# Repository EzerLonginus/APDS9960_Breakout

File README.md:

# APDS9960_Breakout
Breakout for APD29960 Gesture/Prox/Light Sensor.

## Purpose
I had a bunch of these little sensors from an earlier client project.  The project ended up not needed these, and I became the proud owner of a bunch of loose components.  I finally got around to making a simple breakout board for them (It assumes a 3V power source and has no voltage protection of any sort).  
The I2C layout is identical to the OLED boards that I also have a bunch of (and being utilized in the ATTiny412 Metronome project).  The idea being that I could repurpose a metronome board and just plug this in to quickly play with. 

## Scematic

## Layout

## TO DO:
* Populate & test board when it arrives
* Push some test code with the ATTiny412
* Post pictures of finished board

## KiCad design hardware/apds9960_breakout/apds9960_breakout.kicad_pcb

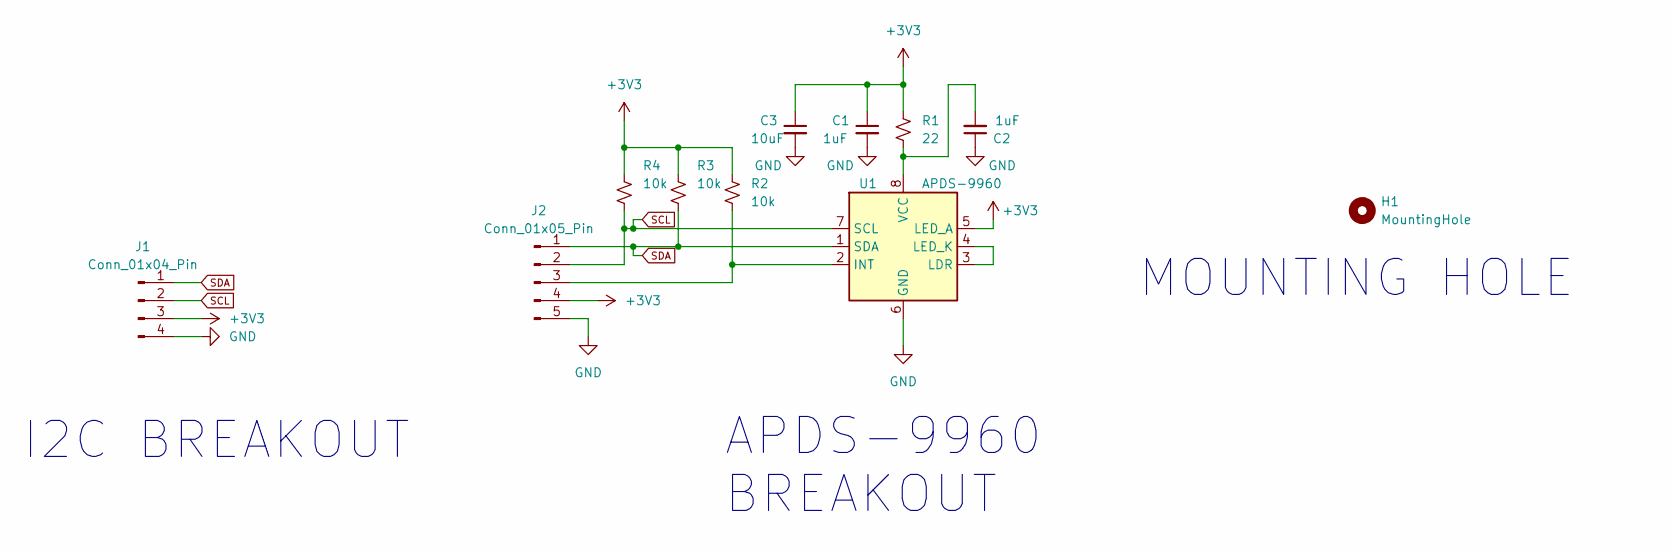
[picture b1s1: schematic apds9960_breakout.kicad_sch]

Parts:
C1, C2: 1uF; C_0603_1608Metric
C3: 10uF; C_0805_2012Metric
H1: MountingHole; MountingHole_3.2mm_M3
J1: Conn_01x04_Pin; PinHeader_1x04_P2.54mm_Vertical
J2: Conn_01x05_Pin; PinHeader_1x05_P2.54mm_Vertical
R1: 22; R_0603_1608Metric
R2, R3, R4: 10k; R_0603_1608Metric
U1: APDS-9960; Avago_APDS-9960

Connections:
+3V3: C1.1, C3.1, J1.3, J2.4, R1.1, R2.1, R3.1, R4.1, U1.5 (LED_A)
GND: C1.2, C2.1, C3.2, J1.4, J2.5, U1.6 (GND)
unnamed: J2.3, R2.2, U1.2 (INT)
unnamed: U1.3 (LDR), U1.4 (LED_K)
unnamed: C2.2, R1.2, U1.8 (VCC)
SCL: J1.2, J2.2, R4.2, U1.7 (SCL)
SDA: J1.1, J2.1, R3.2, U1.1 (SDA)

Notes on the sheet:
I2C BREAKOUT
MOUNTING HOLE
APDS-9960 BREAKOUT

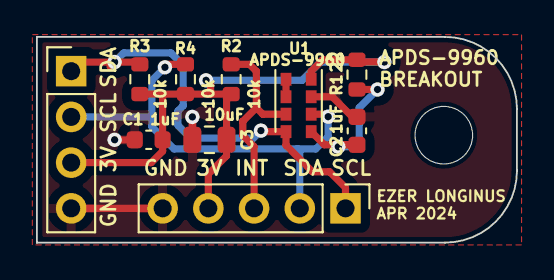
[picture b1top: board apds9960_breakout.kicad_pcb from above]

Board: 2 copper layers, 26.7 x 11.4 mm, 11 parts (0 on the bottom side), 7 nets.

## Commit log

2024-04-25 pin swap
